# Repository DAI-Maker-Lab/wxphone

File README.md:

# wxPhone
wxPhone is an open-source weather station design based on the Seeeduino Stalker V3, Adafruit FONA and BME280 breakout boards, and Ambient Data Systems weather meters. It is a work in progress and is presently being field tested in Silver Spring, Maryland in the United States and Malang, Indonesia.

The design will not work with the newer Stalker V3.1 boards; among other issues they do not supply enough current to power the FONA. This is a problem. The next iteration will use a different microcontroller and a configuration that allows the BME280 board to be mounted separately from the other electronics, so that only the BME280 is exposed to the air.

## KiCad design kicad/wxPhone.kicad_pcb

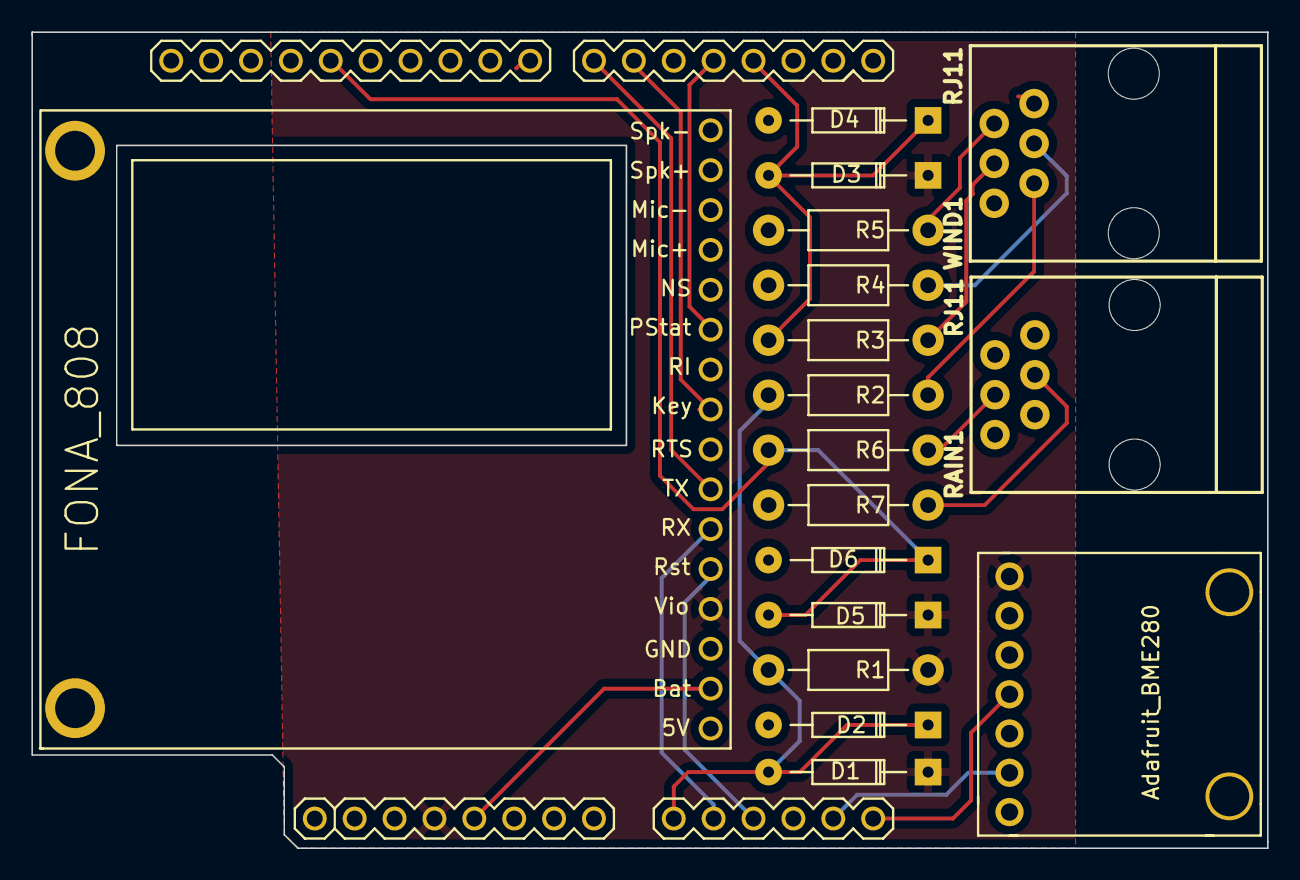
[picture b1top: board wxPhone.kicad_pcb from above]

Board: 2 copper layers, 78.7 x 52.0 mm, 18 parts (0 on the bottom side), 19 nets.

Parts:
D1, D2, D3, D4, D5, D6: DIODE; Diode_DO-35_SOD27_Horizontal_RM10
R1: 4.7K; Resistor_Horizontal_RM10mm
R2, R3, R4, R5, R6, R7: 1K; Resistor_Horizontal_RM10mm
RAIN1: RJ11; RJ11-6
SHIELD1: ARDUINO_SHIELD; ARDUINO
U1: Adafruit_BME280
U2: FONA_808
WIND1: RJ11; RJ11-6

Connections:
3V3: D1.K, D3.K, D5.K, R1.1, SHIELD1.3V3, U1.VIN, U2.4
GND: D2.A, D4.A, D6.A, R4.2, R5.2, R7.2, SHIELD1.GND1, U1.GND, U2.3
unnamed: R2.1, WIND1.2
unnamed: R3.1, WIND1.3
unnamed: R4.1, WIND1.4
unnamed: R5.1, WIND1.5
unnamed: R6.1, RAIN1.3
unnamed: R7.1, RAIN1.4
unnamed: SHIELD1.4, U2.11
unnamed: SHIELD1.6, U2.9
unnamed: SHIELD1.7, U2.7
unnamed: SHIELD1.AD4, U1.SDI
unnamed: SHIELD1.AD5, U1.SCK
RAIN: D5.A, D6.K, R6.2, SHIELD1.13
RST: SHIELD1.AD2, U2.5
RX: SHIELD1.AD1, U2.6
VCC+: SHIELD1.5V, U2.2
WDIR: D1.A, D2.K, R1.2, R2.2, SHIELD1.AD0
WSPEED: D3.A, D4.K, R3.2, SHIELD1.3

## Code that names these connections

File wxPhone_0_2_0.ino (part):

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

#define RTCINT 0                //  RTC interrupt number
#define WDIR A0                 //  Wind direction from vane
#define FONA_RX A1              //  FONA RX pin
#define FONA_RST A2             //  FONA reset pin
#define WSPEED 3                //  Wind speed interrupt pin
#define FONA_TX 7               //  FONA TX pin
#define BEEPIN 5                //  XBee power pin
#define FONA_KEY 6              //  FONA on/off pin
#define FONA_PS 4               //  FONA power status pin
#define RAIN 13                 //  Rain gauge interrupt pin

long lastWindCheck = 0;
volatile long lastWindIRQ = 0;
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
void pciSetup()
{
        //  Setup pin change interrupt for rain pin
        *digitalPinToPCMSK(RAIN) |= bit (digitalPinToPCMSKbit(RAIN));  //   Enable pin
        PCIFR  |= bit (digitalPinToPCICRbit(RAIN)); //    Clear any outstanding interrupt
        PCICR  |= bit (digitalPinToPCICRbit(RAIN)); //    Enable interrupt for the group
}


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        pinMode (FONA_KEY, OUTPUT);
        pinMode (FONA_PS, INPUT);       
        pinMode (FONA_RX, OUTPUT);
        pinMode (WSPEED, INPUT_PULLUP);
        pinMode (RAIN, INPUT_PULLUP);
        pinMode (WDIR, INPUT);


        /*   If the voltage at startup is less than 3.5V, we assume the battery died in the field
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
